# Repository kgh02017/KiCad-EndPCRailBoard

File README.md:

# KiCad-EndPCRailBoard

KiCad6 project files for EndPCRailBoard

## Description

This repositorhy contains KiCad6 project files for EndPCRailBoard.

EndPCRailBoard is designed for TOMIX N-gauge End PC Rail (Dummy type), which doesn't come with a circuit board to light it up.
The board size is the same as the original board which is included in End PC Rail (LED Type).

### Artifacts

- [Schematic](./artifacts/EndPCRailBoard-schematic.pdf)
- [BOM](https://htmlview.glitch.me/?https://github.com/kgh02017/KiCad-EndPCRailBoard/blob/main/project/EndPCRailBoard/bom/EndPCRailBoard.html)

## Arthor

Taku Izumi

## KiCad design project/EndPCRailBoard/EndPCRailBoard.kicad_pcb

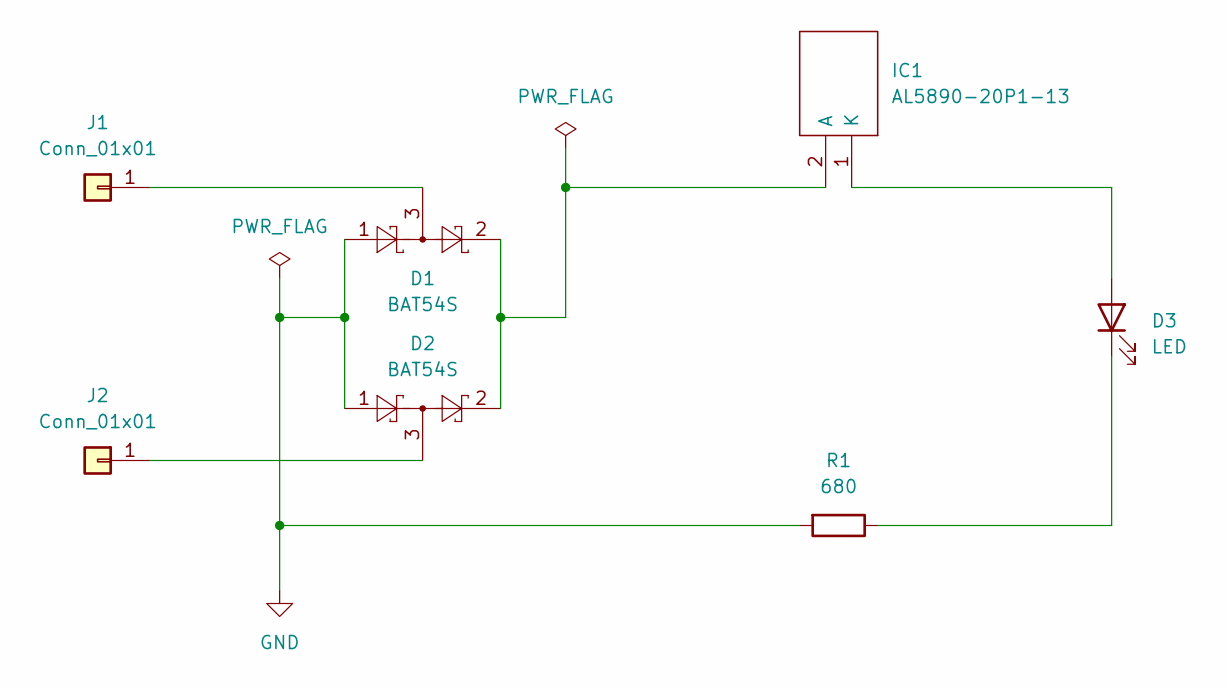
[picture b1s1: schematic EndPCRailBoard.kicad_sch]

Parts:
D1, D2: BAT54S; SOT-23
D3: LED; LED_0805_2012Metric
IC1: AL5890-20P1-13; SODFL3718X100N; Manufacturer_Part_Number AL5890-20P1-13; Mouser Part Number 621-AL5890-20P1-13
J1, J2: Conn_01x01; Solder_Pad_3.0x5.0mm
R1: 680; R_1206_3216Metric

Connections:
GND: D1.1, D2.1, R1.2
unnamed: D1.2, D2.2, IC1.2 (A)
unnamed: D1.3, J1.1
unnamed: D2.3, J2.1
unnamed: D3.1 (K), R1.1
unnamed: D3.2 (A), IC1.1 (K)

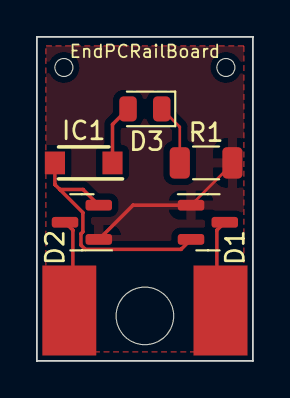
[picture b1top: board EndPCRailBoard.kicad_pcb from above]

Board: 2 copper layers, 12.0 x 18.0 mm, 10 parts (0 on the bottom side), 6 nets.

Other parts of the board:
MH1: MountingHole_3.2mm_M3
MH2, MH3: Hole_1mm

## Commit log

2022-12-10 Add KiCad6 project files for EndPCRailBoard
2022-12-10 Add EndPCrailBoard-PNLZ project
    This patchset adds EndPCRailBoard-PNLZ project which includes
    panerized PCB and gerber data.
2022-12-11 Rename filename of schematic pdf
    This patch changes the filename of schematic pdf
    from "EndPCRailBoard.pdf" to "EndPCRailBoard-schematic.pdf".
